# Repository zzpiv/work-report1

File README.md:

# work-report1
work report
2020.9.28

1. Download and install Arduino IDE, eagle and GitHub clients.

2 passed https://www.tinkercad.com/learn/project-gallery;collectionId=OMOZACHJ9IR8LRE The website has learned the programming format of Arduino, the use of common library of Arduino, code writing and online debugging. The program of lighting and flashing LED light, actuator driver and ultrasonic distance measurement program are compiled.

3. Learn the common functions of GitHub.

2020.9.28
	1.下载并安装了arduino IDE，EAGLE，github客户端。
	2通过https://www.tinkercad.com/learn/project-gallery;collectionId=OMOZACHJ9IR8LRE网站学习了arduino的编程格式，了解了arduino常用库的使用和代码编写，在线调试。编写了点亮并让LED灯闪烁程序，舵机驱动程序，超声波测距程序。
	3.学习了解github的常用功能。
	
2020.9.30
	1.月arduino与mpu6050进行连接，并使用驱动库对mpu6050获得的数据进行欧拉角的转换，在串口上显示姿态解算后的3个欧拉角的变化。

Mpu6050代码：

#include "I2Cdev.h"

#include "MPU6050_6Axis_MotionApps20.h"

MPU6050 mpu;

uint8_t fifoBuffer[64];

Quaternion q;

VectorFloat gravity;    //

float ypr[3];           //姿态解算后存放欧拉角的数组

void setup()
{

  Serial.begin(115200);//设置串口波特率为115200
  
  mpu.initialize();     //以下为库函数的调月，对mpu6050进行初始化
  
  mpu.dmpInitialize();
  
  mpu.CalibrateAccel(6);
  
  mpu.CalibrateGyro(6);
  
  mpu.PrintActiveOffsets();
  
  mpu.setDMPEnabled(true);
  
}

void loop()

{

  if (mpu.dmpGetCurrentFIFOPacket(fifoBuffer))
  
  {
  
    mpu.dmpGetQuaternion(&q, fifoBuffer);
    
    mpu.dmpGetGravity(&gravity, &q);
    
    mpu.dmpGetYawPitchRoll(ypr, &q, &gravity);
    
    Serial.print("ypr\t");                //打印出xyz3个欧拉角数据
    
    Serial.print(ypr[0] * 180 / M_PI);
    
    Serial.print("\t");
    
    Serial.print(ypr[1] * 180 / M_PI);
    
    Serial.print("\t");
    
    Serial.println(ypr[2] * 180 / M_PI);
    
  }
  
}

3.用EAGLE练习画原理图和pcb图的布局布线。

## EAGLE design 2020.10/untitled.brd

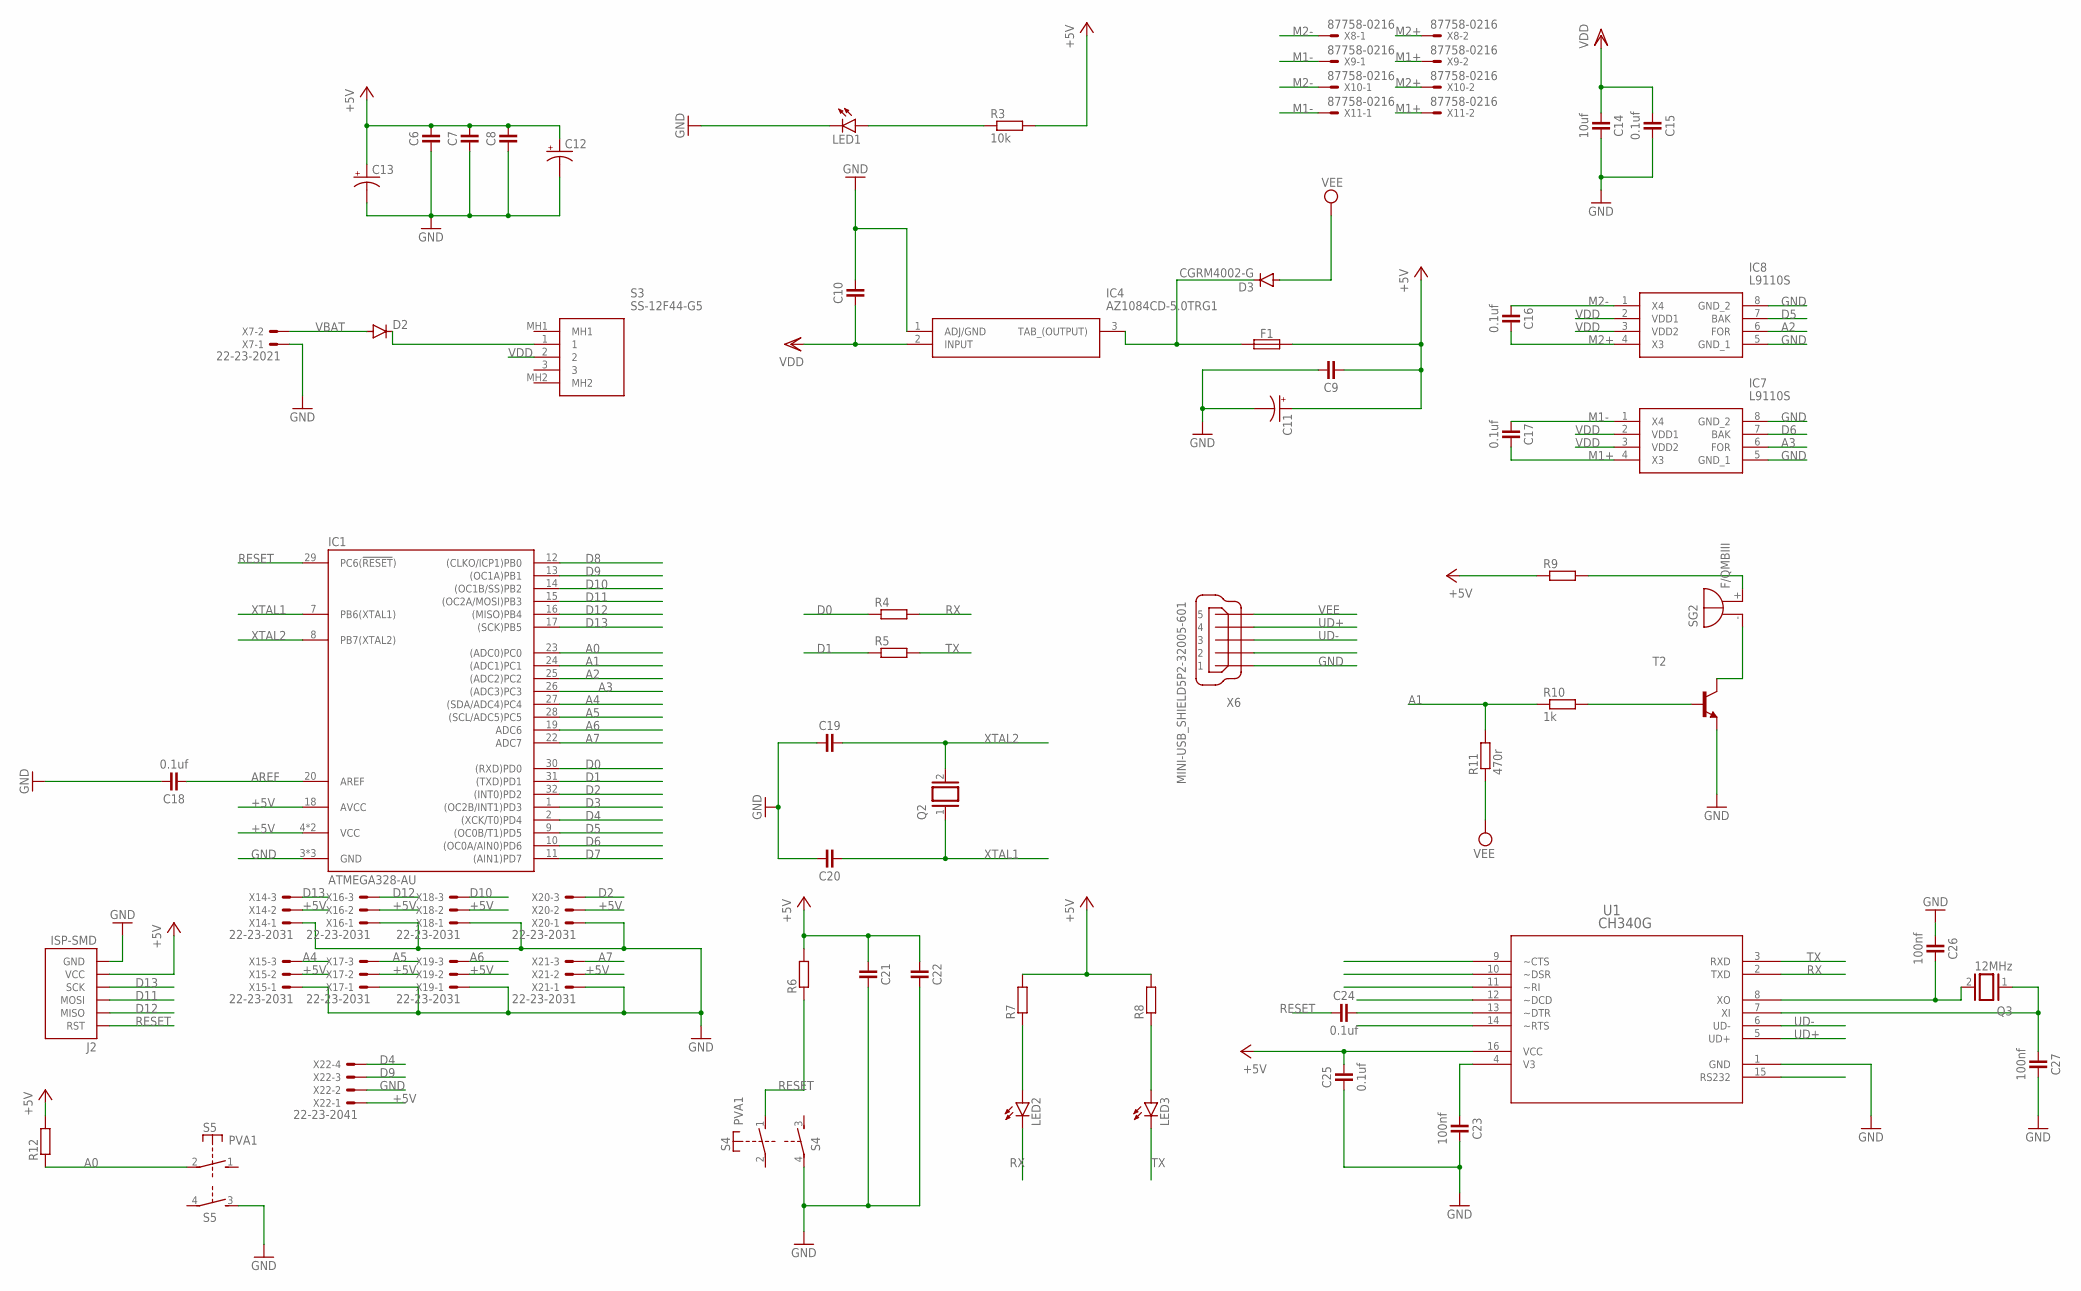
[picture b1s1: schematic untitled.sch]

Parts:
C6, C7, C8, C9, C10, C19, C20, C21, C22: CAPACITOR-0603; C0603
C11, C12, C13: CPOL-USB/3528-21R; B/3528-21R
C14: 10uf; C0603
C15, C16, C17, C18, C24, C25: 0.1uf; C0603
C23, C26, C27: 100nf; C0603
D2: DIODE-DO-214AC; DO-214AC
D3: CGRM4002-G; SOD-123_MINI-SMA
F1: FUSE-1812; C1812
IC1: ATMEGA328-AU; TQFP32
IC4: AZ1084CD-5.0TRG1; TO-252_1
IC7, IC8: L9110S; SOIC127P600X175-8N
J2: ISP-SMD; ISP-2X3_SMD
LED1, LED2, LED3: LEDCHIPLED_0805; CHIPLED_0805
Q2: XTAL/S; QS
Q3: 12MHz; QS
R3: 10k; R0603
R4, R5, R6, R7, R8, R9, R12: R-EU_R0603; R0603
R10: 1k; R0603
R11: 470r; R0603
S3: SS-12F44-G5; SS12F44G5
S4, S5: PVA1; PVA1F
SG2: F/QMBIII
T2: BC817-NPN-SOT23-BEC; SOT23-BEC
U1: CH340G; SOP16-50-062A
X6: MINI-USB_SHIELD5P2-32005-601; 32005-601
X7: 22-23-2021
X8, X9, X10, X11: 87758-0216
X14, X15, X16, X17, X18, X19, X20, X21: 22-23-2031
X22: 22-23-2041

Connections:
+5V: C6.2, C7.2, C8.2, C9.1, C11.+, C12.+, C13.+, C21.1, C22.1, C25.2, F1.2, IC1.4 (VCC), IC1.6 (VCC), IC1.18 (AVCC), J2.VCC, R3.2, R6.2, R7.2, R8.2, R9.1, R12.2, U1.16 (VCC), X14.2, X15.2, X16.2, X17.2, X18.2, X19.2, X20.2, X21.2, X22.1
A0: IC1.23 ((ADC0)PC0), R12.1, S5.2
A1: IC1.24 ((ADC1)PC1), R10.1, R11.2
A2: IC1.25 ((ADC2)PC2), IC8.6 (FOR)
A3: IC1.26 ((ADC3)PC3), IC7.6 (FOR)
A4: IC1.27 ((SDA/ADC4)PC4), X15.3
A5: IC1.28 ((SCL/ADC5)PC5), X17.3
A6: IC1.19 (ADC6), X19.3
A7: IC1.22 (ADC7), X21.3
AREF: C18.1, IC1.20 (AREF)
D0: IC1.30 ((RXD)PD0), R4.1
D1: IC1.31 ((TXD)PD1), R5.1
D2: IC1.32 ((INT0)PD2), X20.3
D3: IC1.1 ((OC2B/INT1)PD3)
D4: IC1.2 ((XCK/T0)PD4), X22.4
D5: IC1.9 ((OC0B/T1)PD5), IC8.7 (BAK)
D6: IC1.10 ((OC0A/AIN0)PD6), IC7.7 (BAK)
D7: IC1.11 ((AIN1)PD7)
D8: IC1.12 ((CLKO/ICP1)PB0)
D9: IC1.13 ((OC1A)PB1), X22.3
D10: IC1.14 ((OC1B/SS)PB2), X18.3
D11: IC1.15 ((OC2A/MOSI)PB3), J2.MOSI
D12: IC1.16 ((MISO)PB4), J2.MISO, X16.3
D13: IC1.17 ((SCK)PB5), J2.SCK, X14.3
GND: C6.1, C7.1, C8.1, C9.2, C10.2, C11.-, C12.-, C13.-, C14.2, C15.2, C18.2, C19.1, C20.2, C21.2, C22.2, C23.2, C25.1, C26.1, C27.2, IC1.3 (GND), IC1.5 (GND), IC1.21 (GND), IC4.1 (ADJ/GND), IC7.5 (GND_1), IC7.8 (GND_2), IC8.5 (GND_1), IC8.8 (GND_2), J2.GND, LED1.C, S4.4, S5.3 (S), T2.E, U1.1 (GND), X6.1, X7.1, X14.1, X15.1, X16.1, X17.1, X18.1, X19.1, X20.1, X21.1, X22.2
M1+: C17.2, IC7.4 (X3), X9.2, X11.2
M1-: C17.1, IC7.1 (X4), X9.1, X11.1
M2+: C16.2, IC8.4 (X3), X8.2, X10.2
M2-: C16.1, IC8.1 (X4), X8.1, X10.1
unnamed: LED1.A, R3.1
unnamed: D2.C, S3.1
unnamed: D3.C, F1.1, IC4.3 (TAB_(OUTPUT))
unnamed: LED2.A, R7.1
unnamed: LED3.A, R8.1
unnamed: C27.1, Q3.1, U1.7 (XI)
unnamed: R9.2, SG2.+ (-)
unnamed: SG2.- (+), T2.C
unnamed: R10.2, T2.B
unnamed: C26.2, Q3.2, U1.8 (XO)
unnamed: C24.2, U1.13 (~DTR)
unnamed: C23.1, U1.4 (V3)
RESET: C24.1, IC1.29 (PC6(!RESET!)), J2.RST, R6.1, S4.1 (S)
RX: LED2.C, R4.2, U1.2 (TXD)
TX: LED3.C, R5.2, U1.3 (RXD)
UD+: U1.5 (UD+), X6.4
UD-: U1.6 (UD-), X6.3
VBAT: D2.A, X7.2
VDD: C10.1, C14.1, C15.1, IC4.2 (INPUT), IC7.2 (VDD1), IC7.3 (VDD2), IC8.2 (VDD1), IC8.3 (VDD2), S3.2
VEE: D3.A, R11.1, X6.5
XTAL1: C20.1, IC1.7 (PB6(XTAL1)), Q2.1
XTAL2: C19.2, IC1.8 (PB7(XTAL2)), Q2.2

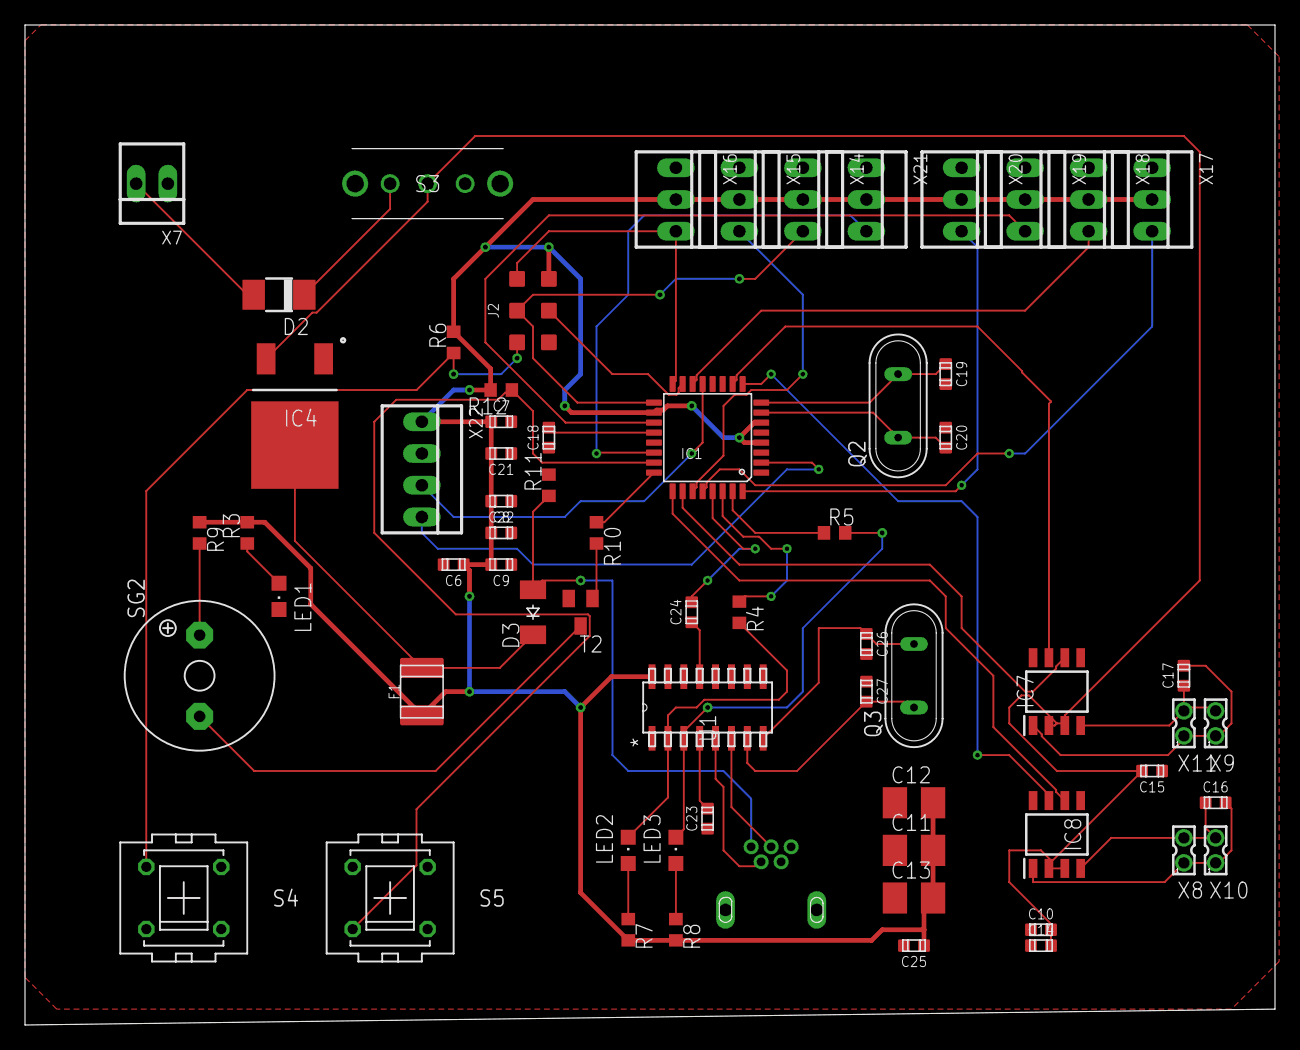
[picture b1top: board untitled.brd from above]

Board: 2 copper layers, 100.0 x 80.0 mm, 66 parts (1 on the bottom side), 48 nets.

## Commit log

2020-09-29 2020.9.28
    work
2020-10-03 Create fullfile
2020-10-04 Create 2020.10
    2020 10 work
2020-10-04 Create mpu6050
    mpu6050
2020-10-14 Create fillfile
2020-10-20 Create fuillfile
2020-10-20 Create fuiill
2020-10-20 Add files via upload
    红外遥控原理图，datasheet，library
2020-10-23 Add files via upload
    按照pcb板子实际尺寸进行修改
